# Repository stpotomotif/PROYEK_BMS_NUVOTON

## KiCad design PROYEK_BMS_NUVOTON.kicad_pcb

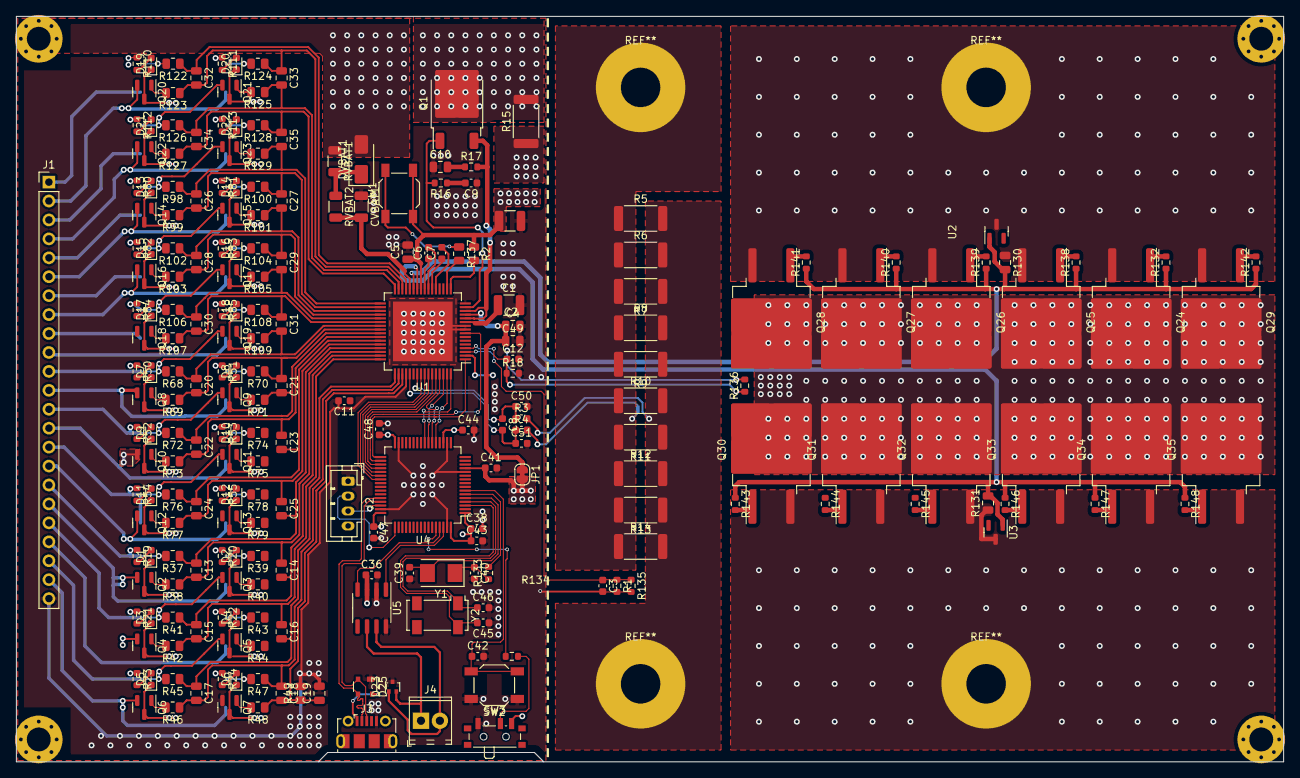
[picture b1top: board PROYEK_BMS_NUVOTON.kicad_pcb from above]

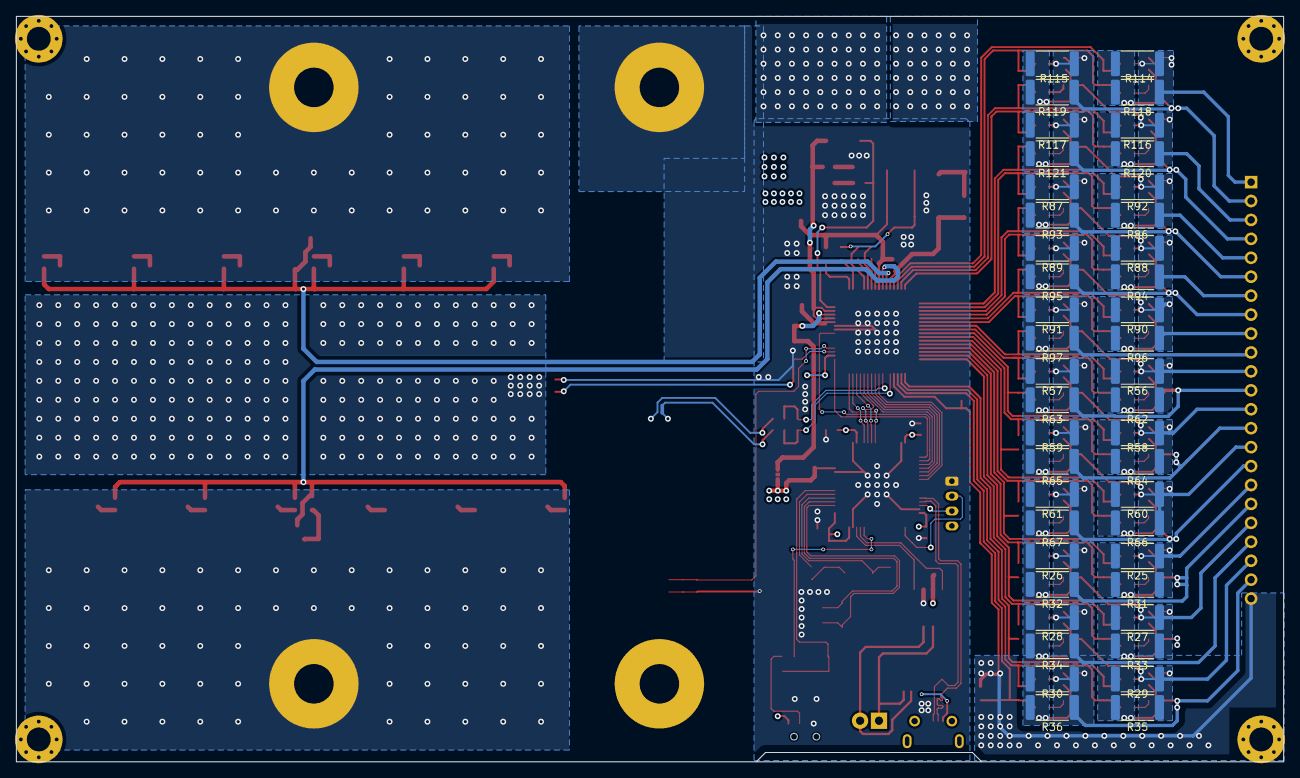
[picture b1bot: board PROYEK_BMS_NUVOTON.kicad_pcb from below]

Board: 4 copper layers, 170.0 x 100.0 mm, 277 parts (45 on the bottom side), 179 nets.

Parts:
C1: 4.7u; C_1210_3225Metric
C2: 1u; C_1210_3225Metric
C3, C12: 1n; C_0603_1608Metric
C4: 1u; C_0805_2012Metric
C5: 0.1u; C_0805_2012Metric
C6, C7: 0.68u; C_0603_1608Metric
C8, C50, C51: 0.1u; C_0603_1608Metric
C9: 22n; C_0603_1608Metric
C10: 10u; C_0805_2012Metric
C11: 100n; C_0603_1608Metric
C13, C14, C15, C16, C17, C18, C19, C20, C21, C22, C23, C24, C25, C26, C27, C28, C29, C30, C31, C32, C33, C34, C35: 180n; C_0805_2012Metric
C36, C38, C41, C42, C43, C44, C47: 100n,0603; C_0603_1608Metric
C39, C40, C45, C46: 20p,0603; C_0603_1608Metric
C48: 4.7u,0603; C_0603_1608Metric
C49: 0.1 uF; C_0805_2012Metric
CVBAT1: 1uF; C_1206_3216Metric
D1, D2, D3, D4, D5, D6, D7, D8, D9, D10, D11, D12, D13, D14, D15, D16, D17, D18, D19, D20, D21, D22: LED; LED_0603_1608Metric
D23: RCLAMP0502B; SOT-416
D25: PRTR5V0U2X; SOT-143
DVBAT1: US1M; D_SMA
J1: Conn_01x23_Pin; PinHeader_1x23_P2.54mm_Vertical
J2: Conn_01x04_Pin; JST_PH_B4B-PH-K_1x04_P2.00mm_Vertical
J3: USB_B_Micro; USB_Micro-B_Molex-105017-0001
J4: Screw_Terminal_01x02; TerminalBlock_Phoenix_MPT-0,5-2-2.54_1x02_P2.54mm_Horizontal
JP1: Jumper_2_Bridged; SolderJumper-2_P1.3mm_Bridged_RoundedPad1.0x1.5mm
NT1: NetTie_2; NetTie-2_SMD_Pad0.5mm
Q1: NPN; TO-252-2
Q2, Q3, Q4, Q5, Q6, Q7, Q8, Q9, Q10, Q11, Q12, Q13, Q14, Q15, Q16, Q17, Q18, Q19, Q20, Q21, Q22, Q23: Q_NMOS_GSD; SOT-23
Q24, Q25, Q26, Q27, Q28, Q29, Q30, Q31, Q32, Q33, Q34, Q35: NMOS; TO-263-2
R1, R18: 47k; R_0603_1608Metric
R2: 30k; R_0805_2012Metric
R3, R4: 100; C_0603_1608Metric
R5, R6, R7, R8, R9, R10, R11, R12, R13, R14: 10m; R_2512_6332Metric
R15: 100; R_2512_6332Metric
R16: 18k; R_0603_1608Metric
R17: 0.1; R_0603_1608Metric
R19, R20, R21, R22, R23, R24, R50, R51, R52, R53, R54, R55, R80, R81, R82, R83, R84, R85, R110, R111, R112, R113: 4k7; R_0603_1608Metric
R25, R26, R27, R28, R29, R30, R31, R32, R33, R34, R35, R36, R56, R57, R58, R59, R60, R61, R62, R63, R64, R65, R66, R67, R86, R87, R88, R89, R90, R91, R92, R93, R94, R95, R96, R97, R114, R115, R116, R117, R118, R119, R120, R121: 36; R_2512_6332Metric
R37, R39, R41, R43, R45, R47, R49, R68, R70, R72, R74, R76, R78, R98, R100, R102, R104, R106, R108, R122, R124, R126, R128: 910; R_0805_2012Metric
R38, R40, R42, R44, R46, R48, R69, R71, R73, R75, R77, R79, R99, R101, R103, R105, R107, R109, R123, R125, R127, R129: 1k; R_0805_2012Metric
R130, R131: 10M; C_0805_2012Metric
R132, R138, R139, R140, R141, R142, R143, R144, R145, R146, R147, R148: 2R2; R_0603_1608Metric
R133: 390,0603; R_0603_1608Metric
R134: 10k,0603; R_0603_1608Metric
R135, R136: NTC10k; R_0603_1608Metric
R137: 75M; R_0805_2012Metric
RVBAT1, RVBAT2: 100; R_1206_3216Metric
SW1, SW2: SW_Push; SW_SPST_SKQG_WithStem
SW3: SW_SPDT; SW_SPDT_PCM12
U1: KA49522; HTQFP-64-1EP_10x10mm_P0.5mm_EP8x8mm
U2, U3: TL431DBZ; SOT-23
U4: STM32F072RBTx; LQFP-64_10x10mm_P0.5mm
U5: SN65HVD230; SOIC-8_3.9x4.9mm_P1.27mm
Y1: 8M,SMD; Crystal_SMD_5032-2Pin_5.0x3.2mm
Y2: 32.768k,SMD; Crystal_SMD_Abracon_ABS25-4Pin_8.0x3.8mm

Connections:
+3V3: C36.1, C38.1, C41.1, C43.1, C44.1, C47.1, C48.1, J2.4, JP1.2 (B), SW3.3 (C), U4.1 (VBAT), U4.13 (VDDA), U4.19 (VDD), U4.32 (VDD), U4.48 (VDDIO2), U4.64 (VDD), U5.3 (VCC)
/BOOT0: R134.2, U4.60 (BOOT0)
/CAN_D+: D23.1 (K1), J4.2, U5.7 (CANH)
/CAN_D-: D23.2 (K2), J4.1, U5.6 (CANL)
/CAN_RX: U4.61 (PB8), U5.4 (R)
/CAN_TX: U4.62 (PB9), U5.1 (D)
/OSC32_IN: C45.2, U4.3 (PC14), Y2.4
/OSC32_OUT: C46.1, U4.4 (PC15), Y2.1
/OSC_IN: C39.2, U4.5 (PF0), Y1.2
/OSC_OUT: R133.2, U4.6 (PF1)
/RESET: C42.1, SW2.2, U4.7 (NRST)
/SWCLK: J2.2, U4.49 (PA14)
/SWDIO: J2.3, U4.46 (PA13)
/USB_D+: D25.2 (I/O1), J3.3 (D+), U4.45 (PA12)
/USB_D-: D25.3 (I/O2), J3.2 (D-), U4.44 (PA11)
ALARM1: U1.59 (ALARM1), U4.36 (PB15)
BMS_3.3V: C4.1, C49.1, JP1.1 (A), U1.2 (CVDD), U1.13 (REGEXT)
C0: C11.1, C18.2, C19.1, R48.1, R49.1, U1.51 (C0)
C1: C17.2, C18.1, R46.1, R47.1, U1.50 (C1)
C2: C16.2, C17.1, R44.1, R45.1, U1.49 (C2)
C3: C15.2, C16.1, R42.1, R43.1, U1.48 (C3)
C4: C14.2, C15.1, R40.1, R41.1, U1.47 (C4)
C5: C13.2, C14.1, R38.1, R39.1, U1.46 (C5)
C6: C13.1, C25.2, R37.1, R79.1, U1.45 (C6)
C7: C24.2, C25.1, R77.1, R78.1, U1.44 (C7)
C8: C23.2, C24.1, R75.1, R76.1, U1.43 (C8)
C9: C22.2, C23.1, R73.1, R74.1, U1.42 (C9)
C10: C21.2, C22.1, R71.1, R72.1, U1.41 (C10)
C11: C20.2, C21.1, R69.1, R70.1, U1.40 (C11)
C12: C20.1, C31.2, R68.1, R109.1, U1.39 (C12)
C13: C30.2, C31.1, R107.1, R108.1, U1.38 (C13)
C14: C29.2, C30.1, R105.1, R106.1, U1.37 (C14)
C15: C28.2, C29.1, R103.1, R104.1, U1.36 (C15)
C16: C27.2, C28.1, R101.1, R102.1, U1.35 (C16)
C17: C26.2, C27.1, R99.1, R100.1, U1.34 (C17)
C18: C26.1, C35.2, R98.1, R129.1, U1.33 (C18)
C19: C34.2, C35.1, R127.1, R128.1, U1.32 (C19)
C20: C33.2, C34.1, R125.1, R126.1, U1.31 (C20)
C21: C32.2, C33.1, R123.1, R124.1, U1.30 (C21)
C22: C32.1, R122.1, U1.29 (C22)
CHG: R130.2, R132.1, R138.1, R139.1, R140.1, R141.1, R142.1, U1.27 (CHG), U2.1 (K)
CLK: U1.63 (SCL), U4.21 (PA5)
CN4_C1: J1.22, Q6.2 (S), R24.1, R30.1, R36.1, R47.2
CN4_C2: J1.21, Q5.2 (S), R23.1, R29.1, R35.1, R45.2
CN4_C3: J1.20, Q4.2 (S), R22.1, R28.1, R34.1, R43.2
CN4_C4: J1.19, Q3.2 (S), R21.1, R27.1, R33.1, R41.2
CN4_C5: J1.18, Q2.2 (S), R20.1, R26.1, R32.1, R39.2
CN4_C6: J1.17, Q13.2 (S), R19.1, R25.1, R31.1, R37.2
CN4_C7: J1.16, Q12.2 (S), R55.1, R61.1, R67.1, R78.2
CN4_C8: J1.15, Q11.2 (S), R54.1, R60.1, R66.1, R76.2
CN4_C9: J1.14, Q10.2 (S), R53.1, R59.1, R65.1, R74.2
CN4_C10: J1.13, Q9.2 (S), R52.1, R58.1, R64.1, R72.2
CN4_C11: J1.12, Q8.2 (S), R51.1, R57.1, R63.1, R70.2
CN4_C12: J1.11, Q19.2 (S), R50.1, R56.1, R62.1, R68.2
CN4_C13: J1.10, Q18.2 (S), R85.1, R91.1, R97.1, R108.2
CN4_C14: J1.9, Q17.2 (S), R84.1, R90.1, R96.1, R106.2
CN4_C15: J1.8, Q16.2 (S), R83.1, R89.1, R95.1, R104.2
CN4_C16: J1.7, Q15.2 (S), R82.1, R88.1, R94.1, R102.2
CN4_C17: J1.6, Q14.2 (S), R81.1, R87.1, R93.1, R100.2
CN4_C18: J1.5, Q23.2 (S), R80.1, R86.1, R92.1, R98.2
CN4_C19: J1.4, Q22.2 (S), R113.1, R117.1, R121.1, R128.2
CN4_C20: J1.3, Q21.2 (S), R112.1, R116.1, R120.1, R126.2
CN4_C21: J1.2, Q20.2 (S), R111.1, R115.1, R119.1, R124.2
CN4_C22: DVBAT1.2 (A), J1.1, Q24.3 (S), Q25.3 (S), Q26.3 (S), Q27.3 (S), Q28.3 (S), Q29.3 (S), R110.1, R114.1, R118.1, R122.2, R130.1, RVBAT1.1, U2.3 (A)
DIS: R131.2, R143.1, R144.1, R145.1, R146.1, R147.1, R148.1, U1.26 (DIS), U3.1 (K)
EN: U1.64 (SEN), U4.24 (PC4)
FETOFF: U1.60 (FETOFF), U4.35 (PB14)
GND: C1.2, C2.2, C3.2, C4.2, C5.2, C9.1, C10.1, C11.2, C12.2, C19.2, C36.2, C38.2, C39.1, C40.2, C41.2, C42.2, C43.2, C44.2, C45.1, C46.2, C47.2, C48.2, C49.2, C50.2, C51.2, CVBAT1.1, D23.3 (A), D25.1 (GND), J1.23, J2.1, J3.5 (GND), NT1.1, Q7.2 (S), R1.2, R5.1, R6.1, R7.2, R8.1, R9.2, R10.1, R11.2, R12.1, R13.2, R14.1, R18.2, R49.2, R135.2, R136.2, SW2.1, SW3.1 (A), U1.9 (MODE), U1.10 (AVSS1), U1.16 (AVSS2), U1.52 (GND), U1.65 (GND), U4.12 (VSSA), U4.18 (VSS), U4.31 (VSS), U4.47 (VSS), U4.63 (VSS), U5.2 (GND), U5.8 (Rs)
GPIO1: U1.56 (GPIO1), U4.39 (PC8)
GPIO2: U1.57 (GPIO2), U4.38 (PC7)
GPIO3: U1.58 (GPIO3), U4.37 (PC6)
NRST: U1.1 (NRST), U4.33 (PB12)
unnamed: C9.2, R16.1
unnamed: C10.2, R17.1
unnamed: C40.1, R133.1, Y1.1
unnamed: D1.2 (A), R19.2
unnamed: D1.1 (K), Q2.3 (D), R25.2, R31.2
unnamed: D2.2 (A), R20.2
unnamed: D2.1 (K), Q3.3 (D), R26.2, R32.2
unnamed: D3.2 (A), R21.2
unnamed: D3.1 (K), Q4.3 (D), R27.2, R33.2
unnamed: D4.2 (A), R22.2
unnamed: D4.1 (K), Q5.3 (D), R28.2, R34.2
unnamed: D5.2 (A), R23.2
unnamed: D5.1 (K), Q6.3 (D), R29.2, R35.2
unnamed: D6.2 (A), R24.2
unnamed: D6.1 (K), Q7.3 (D), R30.2, R36.2
unnamed: D7.2 (A), R50.2
unnamed: D7.1 (K), Q8.3 (D), R56.2, R62.2
unnamed: D8.2 (A), R51.2
unnamed: D8.1 (K), Q9.3 (D), R57.2, R63.2
unnamed: D9.2 (A), R52.2
unnamed: D9.1 (K), Q10.3 (D), R58.2, R64.2
unnamed: D10.2 (A), R53.2
unnamed: D10.1 (K), Q11.3 (D), R59.2, R65.2
unnamed: D11.2 (A), R54.2
unnamed: D11.1 (K), Q12.3 (D), R60.2, R66.2
unnamed: D12.2 (A), R55.2
unnamed: D12.1 (K), Q13.3 (D), R61.2, R67.2
unnamed: D13.2 (A), R80.2
unnamed: D13.1 (K), Q14.3 (D), R86.2, R92.2
unnamed: D14.2 (A), R81.2
unnamed: D14.1 (K), Q15.3 (D), R87.2, R93.2
unnamed: D15.2 (A), R82.2
unnamed: D15.1 (K), Q16.3 (D), R88.2, R94.2
unnamed: D16.2 (A), R83.2
unnamed: D16.1 (K), Q17.3 (D), R89.2, R95.2
unnamed: D17.2 (A), R84.2
unnamed: D17.1 (K), Q18.3 (D), R90.2, R96.2
unnamed: D18.2 (A), R85.2
unnamed: D18.1 (K), Q19.3 (D), R91.2, R97.2
unnamed: D19.2 (A), R110.2
unnamed: D19.1 (K), Q20.3 (D), R114.2, R118.2
unnamed: D20.2 (A), R111.2
unnamed: D20.1 (K), Q21.3 (D), R115.2, R119.2
unnamed: D21.2 (A), R112.2
unnamed: D21.1 (K), Q22.3 (D), R116.2, R120.2
unnamed: D22.2 (A), R113.2
unnamed: D22.1 (K), Q23.3 (D), R117.2, R121.2
unnamed: DVBAT1.1 (K), RVBAT1.2, RVBAT2.1
unnamed: NT1.2, R4.2
unnamed: Q1.2 (C), R15.2
unnamed: Q2.1 (G), R38.2
unnamed: Q3.1 (G), R40.2
unnamed: Q4.1 (G), R42.2
unnamed: Q5.1 (G), R44.2
unnamed: Q6.1 (G), R46.2
unnamed: Q7.1 (G), R48.2
unnamed: Q8.1 (G), R69.2
unnamed: Q9.1 (G), R71.2
unnamed: Q10.1 (G), R73.2
unnamed: Q11.1 (G), R75.2
unnamed: Q12.1 (G), R77.2
unnamed: Q13.1 (G), R79.2
unnamed: Q14.1 (G), R99.2
unnamed: Q15.1 (G), R101.2
unnamed: Q16.1 (G), R103.2
unnamed: Q17.1 (G), R105.2
unnamed: Q18.1 (G), R107.2
unnamed: Q19.1 (G), R109.2
unnamed: Q20.1 (G), R123.2
unnamed: Q21.1 (G), R125.2
unnamed: Q22.1 (G), R127.2
unnamed: Q23.1 (G), R129.2
unnamed: Q24.1 (G), R132.2
unnamed: Q25.1 (G), R138.2
unnamed: Q26.1 (G), R139.2
unnamed: Q27.1 (G), R140.2
unnamed: Q28.1 (G), R141.2
unnamed: Q29.1 (G), R142.2
unnamed: Q30.1 (G), R143.2
unnamed: Q31.1 (G), R144.2
unnamed: Q32.1 (G), R145.2
unnamed: Q33.1 (G), R146.2
unnamed: Q34.1 (G), R147.2
unnamed: Q35.1 (G), R148.2
unnamed: R137.1, SW1.1
unnamed: R134.1, SW3.2 (B)
unnamed: C7.1, U1.22 (CN1)
unnamed: C6.2, U1.23 (CN2)
unnamed: C7.2, U1.21 (CP1)
unnamed: C6.1, U1.24 (CP2)
unnamed: R2.2, U1.17 (LDM)
unnamed: R137.2, U1.18 (VPC)
REGB: Q1.1 (B), R16.2, U1.15 (REGB)
REG_SUP: Q24.2 (D), Q25.2 (D), Q26.2 (D), Q27.2 (D), Q28.2 (D), Q29.2 (D), Q30.2 (D), Q31.2 (D), Q32.2 (D), Q33.2 (D), Q34.2 (D), Q35.2 (D), R15.1
SDI: U1.62 (SDI), U4.23 (PA7)
SDO: U1.61 (SDO), U4.22 (PA6), U4.25 (PC5)
SHDN: U1.8 (SHDN), U4.34 (PB13)
SRN: C8.1, C50.1, R3.1, U1.55 (SRN)
SRP: C8.2, C51.1, R4.1, U1.53 (SRP)
TMON1: C3.1, R1.1, R135.1, U1.3 (TMONI1)
TMON2: C12.1, R18.1, R136.1, U1.4 (TMONI2)
USB_5V: D25.4 (VCC), J3.1 (VBUS)
VBAT-P: CVBAT1.2, RVBAT2.2, U1.28 (VBAT)
VDD18: C1.1, U1.11 (VDD18)
VDD55: Q1.3 (E), R17.2, U1.12 (REGSEL), U1.14 (VDD55)
VPACK+: C2.1, C5.1, Q30.3 (S), Q31.3 (S), Q32.3 (S), Q33.3 (S), Q34.3 (S), Q35.3 (S), R2.1, R131.1, SW1.2, U1.25 (VPACK), U3.3 (A)
VPACK-: R3.2, R5.2, R6.2, R7.1, R8.2, R9.1, R10.2, R11.1, R12.2, R13.1, R14.2

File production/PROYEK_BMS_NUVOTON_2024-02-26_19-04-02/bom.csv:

Designator,Footprint,Quantity,Value,LCSC Part #
C1,1210,1,2.2u,
C10,0805,1,10u,
"C11, C12, C3",0603,3,100n,
"C13, C14, C15, C16, C17, C18, C19, C20, C21, C22, C23, C24, C25, C26, C27, C28, C29, C30, C31, C32, C33, C34, C35",0805,23,180n,
C2,1210,1,1u,
"C36, C37",0603,2,"1u,0603",
"C38, C41, C42, C43, C44, C47",0603,6,"100n,0603",
"C39, C40, C45, C46",0603,4,"20p,0603",
C4,0805,1,1u,
C48,0603,1,"4.7u,0603",
"C5, C8",0805,2,0.1u,
"C6, C7",0603,2,0.68u,
C9,0603,1,22n,
"D1, D10, D11, D12, D13, D14, D15, D16, D17, D18, D19, D2, D20, D21, D22, D3, D4, D5, D6, D7, D8, D9",0603,22,LED,
D23,SOT-416,1,RCLAMP0502B,
D24,0603,1,GREEN_LED,
D25,SOT-143,1,PRTR5V0U2X,C12333
J2,JST_PH_B4B-PH-K_1x04_P2.00mm_Vertical,1,Conn_01x04_Pin,
J3,USB_Micro-B_Molex-105017-0001,1,USB_B_Micro,
J4,"TerminalBlock_Phoenix_MPT-0,5-2-2.54_1x02_P2.54mm_Horizontal",1,Screw_Terminal_01x02,
Q1,TO-252-2,1,NPN,C140579
"Q10, Q11, Q12, Q13, Q14, Q15, Q16, Q17, Q18, Q19, Q2, Q20, Q21, Q22, Q23, Q3, Q4, Q5, Q6, Q7, Q8, Q9",SOT-23,22,Q_NMOS_GSD,
"Q24, Q25, Q26, Q27, Q28, Q29, Q30, Q31, Q32, Q33, Q34, Q35",TO-263-2,12,NMOS,
R1,0603,1,NTC10k,
"R10, R11, R12, R13, R14, R5, R6, R7, R8, R9",2512,10,10m,
"R100, R102, R104, R106, R108, R122, R124, R126, R128, R37, R39, R41, R43, R45, R47, R49, R68, R70, R72, R74, R76, R78, R98",0805,23,910,
"R101, R103, R105, R107, R109, R123, R125, R127, R129, R38, R40, R42, R44, R46, R48, R69, R71, R73, R75, R77, R79, R99",0805,22,1k,
"R110, R111, R112, R113, R19, R20, R21, R22, R23, R24, R50, R51, R52, R53, R54, R55, R80, R81, R82, R83, R84, R85",0603,22,4k7,
"R114, R115, R116, R117, R118, R119, R120, R121, R25, R26, R27, R28, R29, R30, R31, R32, R33, R34, R35, R36, R56, R57, R58, R59, R60, R61, R62, R63, R64, R65, R66, R67, R86, R87, R88, R89, R90, R91, R92, R93, R94, R95, R96, R97",2512,44,36,
"R130, R131",0805,2,10M,
R132,0603,1,"1.2k,0603",
R133,0603,1,"390,0603",
R134,0603,1,"10k,0603",
R15,2512,1,100,
R16,0603,1,18k,
R17,0603,1,0.1,
R18,0603,1,R,
"R2, R3, R4",0805,3,100,
SW1,SW_100SP1T1B1M1QEH,1,SW_SPDT,
SW2,SW_SPST_PTS645,1,SW_Push,
SW3,SW_CuK_OS102011MA1QN1_SPDT_Angled,1,SW_SPDT,
"U2, U3",SOT-23,2,TL431DBZ,
U4,LQFP-64_10x10mm_P0.5mm,1,STM32F072RBTx,
U5,SOIC-8_3.9x4.9mm_P1.27mm,1,SN65HVD230,
Y1,Crystal_SMD_5032-2Pin_5.0x3.2mm,1,"8M,SMD",
Y2,Crystal_SMD_Abracon_ABS25-4Pin_8.0x3.8mm,1,"32.768k,SMD",

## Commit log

2024-03-03 first init
2024-03-04 revision 2, 12 error fix on bms connection with STM32, USB circuit need some adjustment
2024-03-04 add gitignore and README
2024-03-11 revision 7 March
2024-04-15 revision 11 march
